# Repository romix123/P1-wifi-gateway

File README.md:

P1 wifi gateway 2022
  
  Deze software brengt verschillende componenten bij elkaar in een handzaam pakket.
  
  De software draait op een ESP8285 of ESP8266 en heeft een bescheiden voetafdruk.
  
  De data processing is gebaseerd op: http://domoticx.com/p1-poort-slimme-meter-data-naar-domoticz-esp8266/
  De captive portal is gebaseerd op een van de ESP8266 voorbeelden, de OTA eenheid eveneens.
  
  De module levert data aan een host via JSON of MQTT messages, maar kan ook via de webinterface van de module of via telnet worden uitgelezen
  
  De module zal bij opstarten eerst de buffercondensator laden. 
  Vervolgens knippert hij 2x en zal eerst proberen te koppelen aan je wifi netwerk. Gedurende dat proces zal de LED knipperen
  met een periode van 0.5 Hz.
  Wanneer geen verbinding kan worden gemaakt start de modiule een Access point onder de naam P1_Setup
  Verbind met dit netwerk en surf naar 192.168.4.1
  
  Het menuscherm van de module verschijnt dan. Vul daar SSID en wachtwoord van je wifi netwerk in. 
  Daaronder vul je gegevens van de ontvangede server in (IP en poortnummer). Dit kan je DOmotociz server zijn
  In dat geval moet je ook het IDx dat Domoticz maakt voor een Gas device en een Energy device invoeren.
  Tenslotte geef je aan per hoeveel seconde je data naar de server wilt laten sturen.
  DSMR4 meters hanteren een meetinterval van 10 sec. SMR5 meters leveren iedere seconde data. Dat lijkt me wat veel en 
  kost de module ook veel stroom waardoor het maar de vraag is of hij parasitair (door de meter gevoed) kan werken.
  Ik raad een interval van 15 sec of hoger aan. Het interval dat je hier invoert zal niet altijd synchroon lopen met
  het data interval van de meter, ga er dus niet van uit dat je exact iedere x seconden een meetwaarde ziet in DOmoticz. 
  Tussen metingen 'slaapt' de module (de modem wordt afgeschakeld waardoor het stroomverbruik van zo'n 70mA terugvalt naar 15 mA). 
  Dit geeft de bufferelco tijd om op te laden voor de stroompiekjes die de wifi zender van de module produceert 
  (en het bespaart hoe dan ook wat stroom (die weliswaar door je energieleverancier wordt betaald, maar toch). Alle kleine 
  beetjes helpen..
 
   informatie, vragen, suggesties ed richten aan ronaldleenes@icloud.com
   
   default adminpassword: adminpwd
   
   Zie http://esp8266thingies.nl voor meer informatie over de module en
   http://www.esp8266thingies.nl/wp/forum-2/ voor het disussieforum

 @file P1WG_IDE_2.ino
 @author Ronald Leenes
 @date 22.09.2023
 @version 1.1e 
   
	1.1.e: fixed passwd length related issues (adminpass, SSID, MQTT), worked on wifi persistance, 
			disabled wifi powermanagment, removed multilingual support for now
    1.1d: moved codebase to IDE 2.2, small fixes, added webdebug 

   1.1adc: implemented extensive logging
   			updated Swedish version to align with Dutch version (German and French versions lack security features on setup/update)
   1.1aa: bug fixes
   1.1: implemented graphs
   		fixed reporting tariffIndicatorElectricity
   
   ud: fixed refreshheaders
   ua: fixed setup field issue  
   u: - added password protection for Setup and Update Firmware menus. On first boot of version 1.0u, go to Setup menu 
        within 60 seconds to bypass password protection.
      - added out of the box support for Home Assistant "DSMR Reader" integration. Use 'dsmr' as MQTT prefix and data will
        automatically be delivered in "DSMR Reader" format to the MQTT broker.
      - fixed MQTT reconnect, it is now non-blocking.
      - fixed hardboot daycounters reset
      - fixed sending empty MQTT messages
      - overall improved stability
      
   t: improvements on powermanagement, overall (minor) cleanup
   ta: fix for Telnet reporting
 		added French localisation
   
   s: added German localisation
         Added mqtt output for Swedish specific OBIS codes
         
   r: speed improvements and streamlining of the parser
       localisations for: NL, SE
       
   q: added daily values
   p: incorporated equipmentID in mqtt set
   o: fixed gas output, fixed mqtt reconnect
   n: empty call to SetupSave now redirects to main menu instead of resetting settings ;-)
       fixed kWh/Wh inversion
   m: setupsave fix, relocate to p1wifi.local na 60 sec 
       mqtt - kw/W fix
   l: wifireconnect after wifi loss
   k: fixed big BUG, softAP would not produce accessible webserver.
   j: raw data on port 23
       major code rewrite
       implemented data reporting methods: 
         parsed data: json, mqtt, p1wifi.local/P1
         raw data: telnet on port 23, p1wifi.local/Data
         
   i:  extended max line length for TD210-D meters, which have a really loong 1-0:99.97.0 line
   h:  extended mqtt set with instant powers, voltages, actual tarif group. power outages, power drops
   g: fixed mqtt
   
   Generic ESP8285 module 
	Flash Size: 2mb (FS: 128Kb, OTA: –960Kb) 
   
   needed files: 
   this one (obv), 
   CRC16.h
   JSON.ino
   MQTT.ino
   TELNET.ino
   debug.ino
   decoder.ino
   functions.ino
   graph.ino
   webserver.ino
   webserverNL.ino
   wifi.ino

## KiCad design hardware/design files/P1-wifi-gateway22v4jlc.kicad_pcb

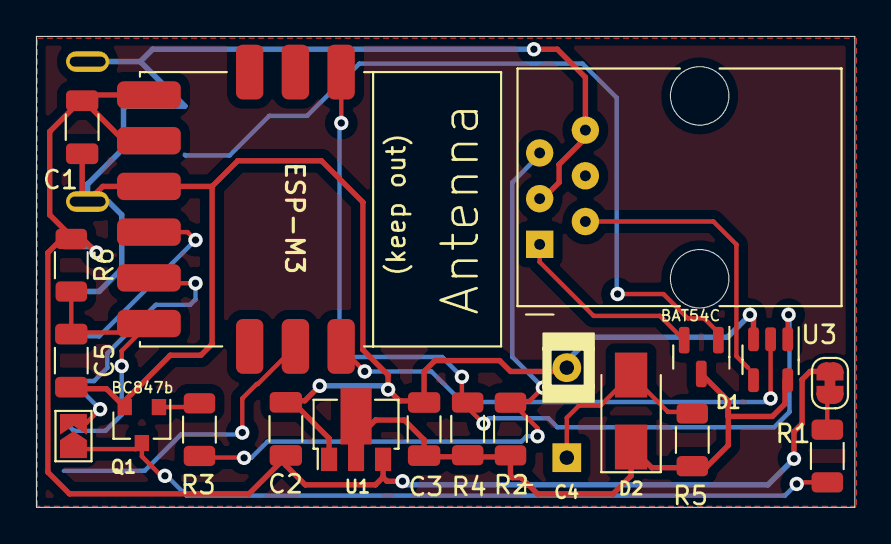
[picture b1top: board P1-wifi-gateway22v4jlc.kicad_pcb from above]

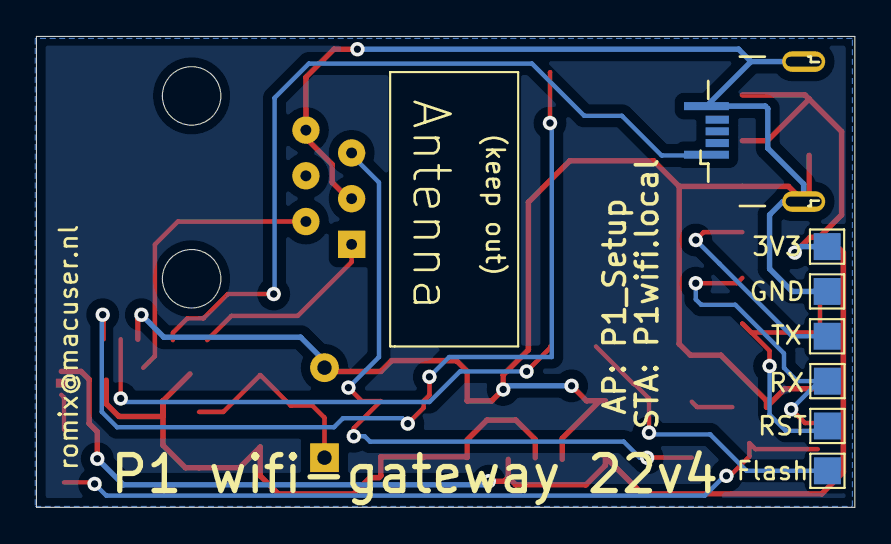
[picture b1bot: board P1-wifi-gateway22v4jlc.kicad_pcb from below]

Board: 2 copper layers, 45.5 x 26.2 mm, 27 parts (7 on the bottom side), 17 nets.

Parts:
C1: 100n; C_1206_3216Metric
C2: 10u; C_1206_3216Metric
C3, C5: 22uF; C_1206_3216Metric
C4: 3300uF; CP_Radial_D8.0mm_P5.00mm
D1: BAT54C; SOT-23
D2: SS14; D_SMA
J1: 6P6C; RJ12_Amphenol_54601
J3: USB_OTG; USB_Micro-B_Ali_power_only
JP1: SolderJumper_2_Bridged; SolderJumper-2_P1.3mm_Bridged_RoundedPad1.0x1.5mm
JP2: SolderJumper_2_Open; SolderJumper-2_P1.3mm_Open_TrianglePad1.0x1.5mm
Q1: BC847b; SOT-23
R1, R2: 2K2; R_1206_3216Metric
R3: 1K; R_1206_3216Metric
R4: 10k; R_1206_3216Metric
R5: 52.3; R_1206_3216Metric
R6: 100k; R_1206_3216Metric
TP1: 3V3; TestPoint_Pad_1.5x1.5mm
TP2: RX; TestPoint_Pad_1.5x1.5mm
TP3: TX; TestPoint_Pad_1.5x1.5mm
TP4: Flash; TestPoint_Pad_1.5x1.5mm
TP5: GND; TestPoint_Pad_1.5x1.5mm
TP6: RST; TestPoint_Pad_1.5x1.5mm
U1: ME6249A33PG; SOT-89-3
U2: ESP-M3
U3: 74AHCT1G125; SOT-23-5

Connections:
+3V3: C1.1, C2.1, JP1.2 (B), R6.1, TP1.1, U1.3 (VO), U2.4 (EN), U2.5 (VCC)
+5V: C3.1, D1.3, D2.1 (K), R2.1, R4.1, R5.1, U1.2 (VI), U3.5 (VCC)
/FLASH: TP4.1, U2.11 (IO0)
/RST: C5.1, R6.2, TP6.1, U2.9 (RST)
/RX: JP2.2 (B), TP2.1, U2.8 (RXD)
/TX: TP3.1, U2.7 (TXD)
GND: C1.2, C2.2, C3.2, C4.2, C5.2, J1.3, J1.6, J3.5 (GND), J3.6 (Shield), Q1.2 (E), TP5.1, U1.1 (GND), U2.6 (GND), U3.3 (GND)
unnamed: C4.1, D2.2 (A), R5.2
unnamed: D1.1, J3.1 (VBUS)
unnamed: D1.2, J1.1
unnamed: J1.2, U3.4
unnamed: J1.5, R2.2, R3.2
unnamed: JP1.1 (A), R1.1
unnamed: JP2.1 (A), Q1.3 (C), R1.2
unnamed: Q1.1 (B), R3.1
unnamed: R4.2, U2.1 (IO16), U3.1
unnamed: U2.12 (IO4), U3.2

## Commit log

2022-07-26 initial commit
    public release van de firmware
2022-07-26 Update README.md
    clean-up
2022-08-01 versie 1.0m
    m: setupsave fix, relocate to p1wifi.local na 60 sec
    * mqtt - kw/W fix
2022-08-02 small fix
    menu button in setup screen fix
2022-08-03 bugfixes
    fixed settings mess-up when calling SetupSave in browser, fixed kWh/Wh setting, fixed P1 reporting window
2022-08-03 Rename .gitingnore to .gitignore
2022-08-30 updates and fixes
    updates and fixes
2022-08-30 cleanup
    update
2022-10-23 lots of changes
    Localisations for Nederlands, German, Swedish.
    lots of small fixes. Still not done with start-up powermanagement.
2022-11-18 Version 1.0t
    Many rewrites and bugfixes
2022-11-21 version 1.0ta
    telnet bugfix
2022-11-21 filename changes
2022-11-28 FR localisation and fixes
2022-11-28 version 1.0ta_DE
2022-12-05 Upgrade the size of the password from 30 to 64
    To be compatible with the standard of the Wifi
2023-01-01 version 1.0u updates
    Significant extra's and bugfixes.
2023-01-05 bugfixes u-> ua
    corrected writing wrongly sized parameters to EEPROM
2023-01-05 small fix
2023-01-08 fixes
2023-01-08 bugfixes
2023-01-11 small fixes
2023-01-23 v1.1: implemented local logging and graphs (and bugfixes)
    Meter data will now be logged on the module's LittleFS file system in hourly, daily (for a week, month and entire year) format. Logfiles can be downloaded and displayed in graphical form locally, so 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
2023-01-24 bug fixes
2023-02-13 logging features/graph extensions
    Logging finally seems to work continuously. Swedish version updated to include passwd on Setup/Update.
2023-02-16 interim version
    basis done for cleaner localisation
2023-02-22 move to spiffs
2023-03-07 Added admin password
2023-03-15 bug fixes
    bug fixes
2023-05-20 support for ISKRA M550E-1011
    1.1be: added support for ISKRA /ISK5\2M550E-1011 (which terminates 1-0.2.7.0 and 1-0:22.7.0 without *, using kW instead)
2023-05-21 ISKRA second attempt
    pick up ISKRA header and treat some data in the telegram differently than for regular 5.0 meters
2023-08-14 small updates
2023-09-22 Telnet upgraded to multiple connections, cleanups
2023-11-15 move to IDE 2.2
    Moved firmware to IDE 2.2
2023-11-15 small fixes
    version correction and debug version
2023-11-15 repo cleanup (a bit)
2023-11-22 Added support for PlatformIO, VSCode and CLion
2023-11-22 Formatted code with Document formatter
2023-11-23 migration to platform IO
    cleanup
2023-11-25 Work in progress !
2023-11-27 major overhaul of OBIS decoder system
    major overhaul in progress
2023-11-27 version 1.2 new OBIS decoder
    code cleanup
2024-01-25 Fix build warnings
2024-02-04 Added Configurable logger
2024-02-11 Improved logging with colors
2024-02-16 Split LED and crc32 functions and other cleanups
2024-02-21 Removed duplicate blink function
2024-03-27 meter id fix
    Meter iD fix
2024-05-11 Added platformio esp8285 board
2024-05-11 Added DSMR mock ability
2024-05-11 Several fixes + Added vscode settings file to gitignore
2024-05-13 clean-up
2024-05-20 WiFi
2024-06-28 Fixing INVALID CRC FOUND due unterminated string
2024-07-21 current Arduino build
    Huidge Arduino build. Deze versie loopt achter op de platformIO versie
2024-07-28 P1 data to struct
2024-09-01 fixed tariff indicator
    small fix
2024-12-16 Narfight builds
